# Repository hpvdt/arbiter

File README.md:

# Arbiter lighting system
Collection of hardware files for the analog lighting system used on Arbiter

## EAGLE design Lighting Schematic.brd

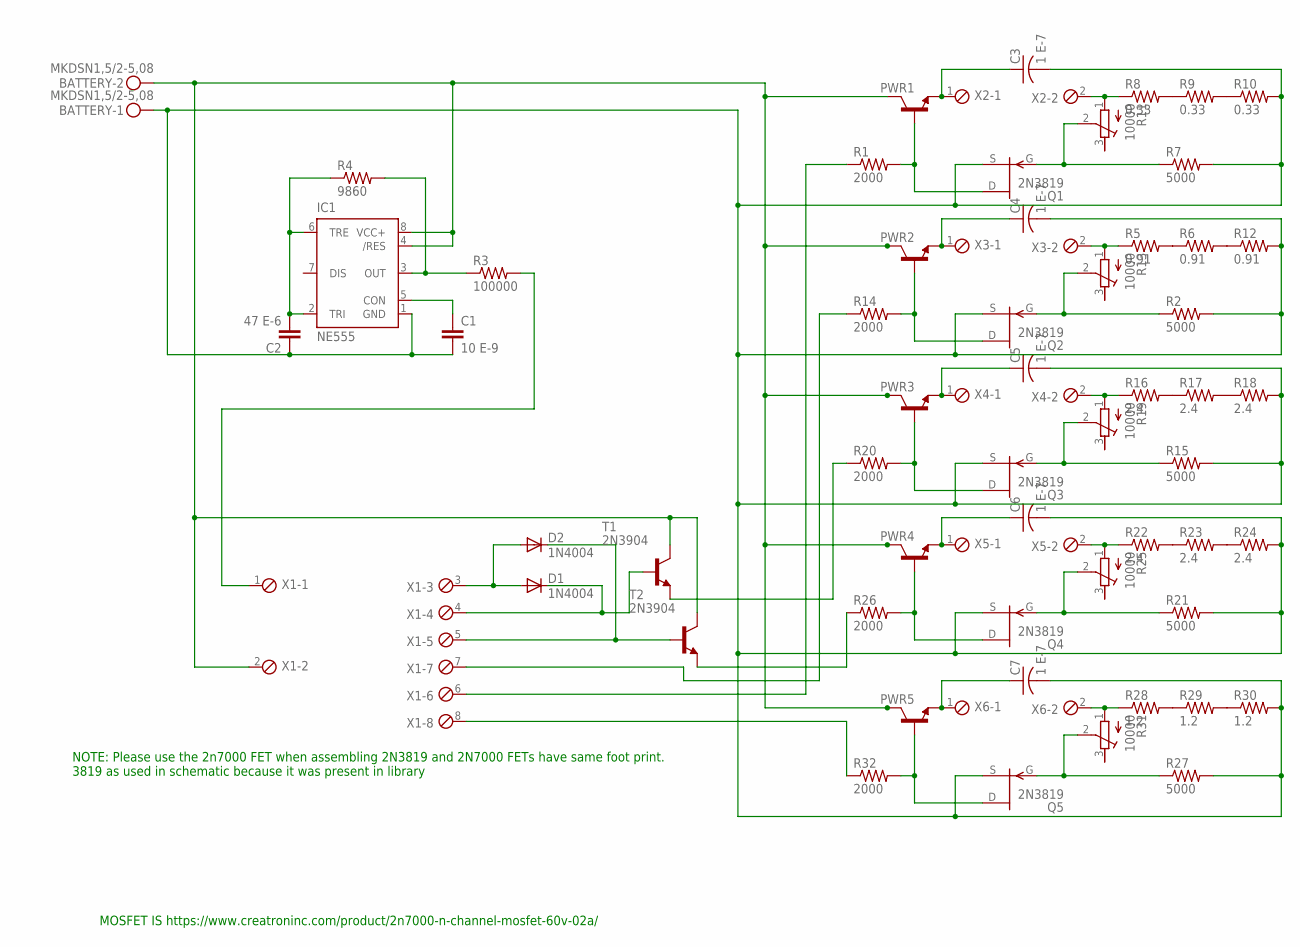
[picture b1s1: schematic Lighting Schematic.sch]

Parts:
BATTERY: MKDSN1,5/2-5,08
C1: 10 E-9; C2.5-5
C2: 47 E-6; C2.5-5
C3, C4, C5, C6, C7: 1 E-7; C075-052X106
D1, D2: 1N4004; DO41-10
IC1: NE555; DIL-08
PWR1, PWR2, PWR3, PWR4, PWR5: -NPN-TO220V; TO220V
Q1, Q2, Q3, Q4, Q5: 2N3819; TO92
R1, R14, R20, R26, R32: 2000; 0207/15
R2, R7, R15, R21, R27: 5000; 0207/10
R3: 100000; 0207/10
R4: 9860; 0207/10
R5, R6, R12: 0.91; P0817V
R8, R9, R10: 0.33; P0817V
R11, R13, R19, R25, R31: 10000; RTRIM3296W
R16, R17, R18, R22, R23, R24: 2.4; P0817V
R28, R29, R30: 1.2; P0817V
T1, T2: 2N3904; TO92
X1: MPT8; 8POL254
X2, X3, X4, X5, X6: MPT2; 2POL254

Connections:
GND: BATTERY.1, C1.2, C2.1, C3.2, C4.2, C5.2, C6.2, C7.2, IC1.1 (GND), Q1.3 (S), Q2.3 (S), Q3.3 (S), Q4.3 (S), Q5.3 (S), R2.2, R7.2, R10.2, R12.2, R15.2, R18.2, R21.2, R24.2, R27.2, R30.2
HEAD+: C4.1, PWR2.3 (E), X3.1
HEAD-: R5.1, R13.1 (A), X3.2
HIGH+: C3.1, PWR1.3 (E), X2.1
HIGH-: R8.1, R11.1 (A), X2.2
LEFT+: C5.1, PWR3.3 (E), X4.1
LEFT-: R16.1, R19.1 (A), X4.2
unnamed: R5.2, R6.1
unnamed: C1.1, IC1.5 (CON)
unnamed: R6.2, R12.1
unnamed: C2.2, IC1.2 (TRI), IC1.6 (TRE), R4.1
unnamed: IC1.3 (OUT), R3.1, R4.2
unnamed: D1.A, D2.A, X1.3
unnamed: D1.C, T1.2 (B), X1.4
unnamed: D2.C, T2.2 (B), X1.5
unnamed: R3.2, X1.1
unnamed: R8.2, R9.1
unnamed: R9.2, R10.1
unnamed: PWR1.1 (B), Q1.1 (D), R1.2
unnamed: Q1.2 (G), R7.1, R11.2 (S)
unnamed: PWR2.1 (B), Q2.1 (D), R14.2
unnamed: Q2.2 (G), R2.1, R13.2 (S)
unnamed: R1.1, X1.6
unnamed: R14.1, X1.7
unnamed: R26.1, T2.3 (E)
unnamed: R32.1, X1.8
unnamed: R16.2, R17.1
unnamed: R17.2, R18.1
unnamed: PWR3.1 (B), Q3.1 (D), R20.2
unnamed: Q3.2 (G), R15.1, R19.2 (S)
unnamed: R22.2, R23.1
unnamed: R23.2, R24.1
unnamed: PWR4.1 (B), Q4.1 (D), R26.2
unnamed: Q4.2 (G), R21.1, R25.2 (S)
unnamed: R28.2, R29.1
unnamed: R29.2, R30.1
unnamed: PWR5.1 (B), Q5.1 (D), R32.2
unnamed: Q5.2 (G), R27.1, R31.2 (S)
unnamed: R20.1, T1.3 (E)
RIGHT+: C6.1, PWR4.3 (E), X5.1
RIGHT-: R22.1, R25.1 (A), X5.2
TAIL+: C7.1, PWR5.3 (E), X6.1
TAIL-: R28.1, R31.1 (A), X6.2
VCC: BATTERY.2, IC1.4 (/RES), IC1.8 (VCC+), PWR1.2 (C), PWR2.2 (C), PWR3.2 (C), PWR4.2 (C), PWR5.2 (C), T1.1 (C), T2.1 (C), X1.2

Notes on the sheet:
MOSFET IS https://www.creatroninc.com/product/2n7000-n-channel-mosfet-60v-02a/
NOTE: Please use the 2n7000 FET when assembling 2N3819 and 2N7000 FETs have same foot print. 3819 as used in schematic because it was present in library

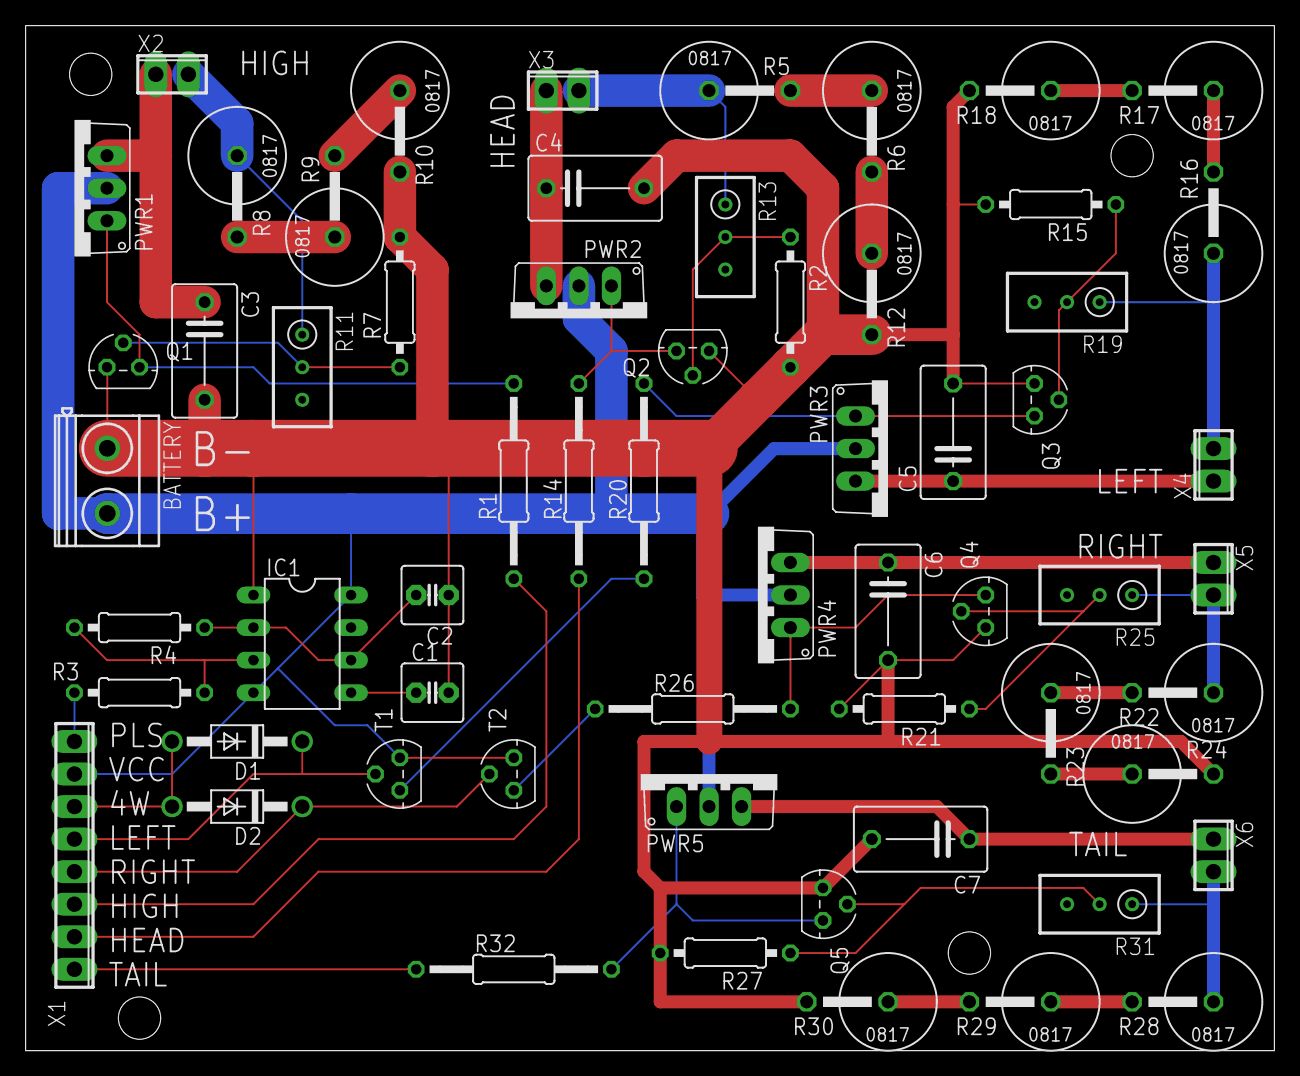
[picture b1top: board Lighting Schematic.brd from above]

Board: 2 copper layers, 97.5 x 80.0 mm, 61 parts (0 on the bottom side), 44 nets.
